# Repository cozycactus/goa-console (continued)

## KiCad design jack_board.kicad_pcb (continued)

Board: 2 copper layers, 8 parts (3 on the bottom side), 8 nets, no tracks yet.

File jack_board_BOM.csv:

"Qty","Value","Footprint","MPN","DNP","References"
"2","100p C0G","Capacitor_SMD:C_0805_2012Metric","","","C8 C9"
"1","Main board link 2x5","Connector_IDC:IDC-Header_2x05_P2.54mm_Vertical","Wurth 61201021621 (2x5 box header)","","CN5"
"1","Line in TRS","Connector_Audio:Jack_6.35mm_Neutrik_NJ6FD-V_Vertical","Neutrik NJ6FD-V","","J1"
"1","Insert TRS switched","Connector_Audio:Jack_6.35mm_Neutrik_NJ6FD-V_Vertical","Neutrik NJ6FD-V","","J2"
"1","Direct out TRS","Connector_Audio:Jack_6.35mm_Neutrik_NJ6FD-V_Vertical","Neutrik NJ6FD-V","","J5"

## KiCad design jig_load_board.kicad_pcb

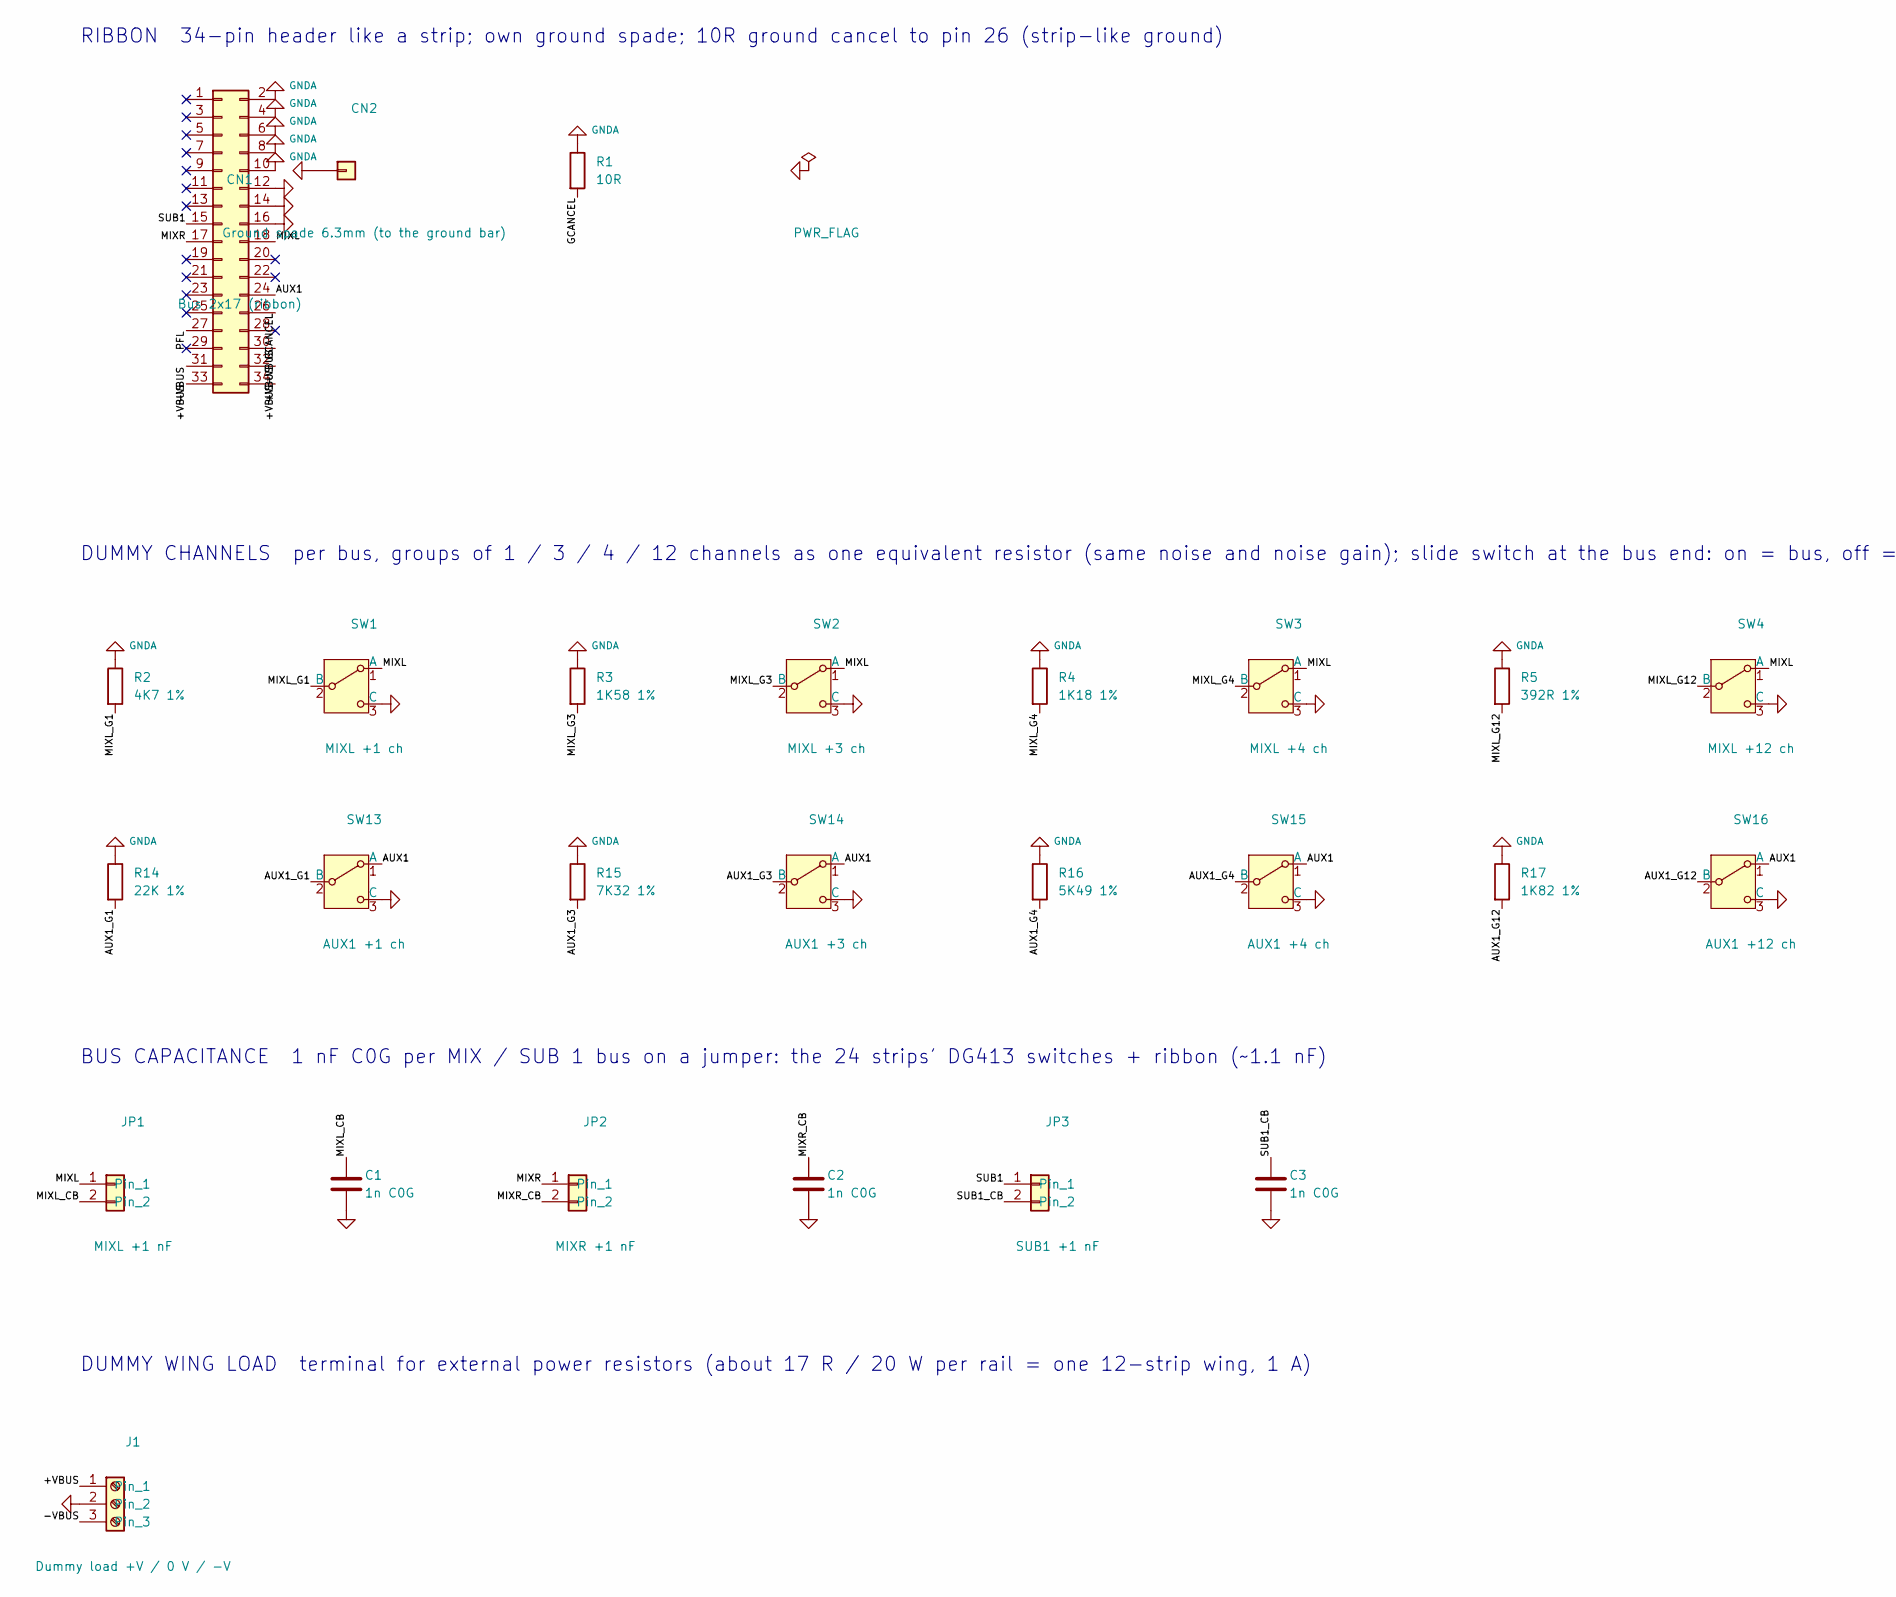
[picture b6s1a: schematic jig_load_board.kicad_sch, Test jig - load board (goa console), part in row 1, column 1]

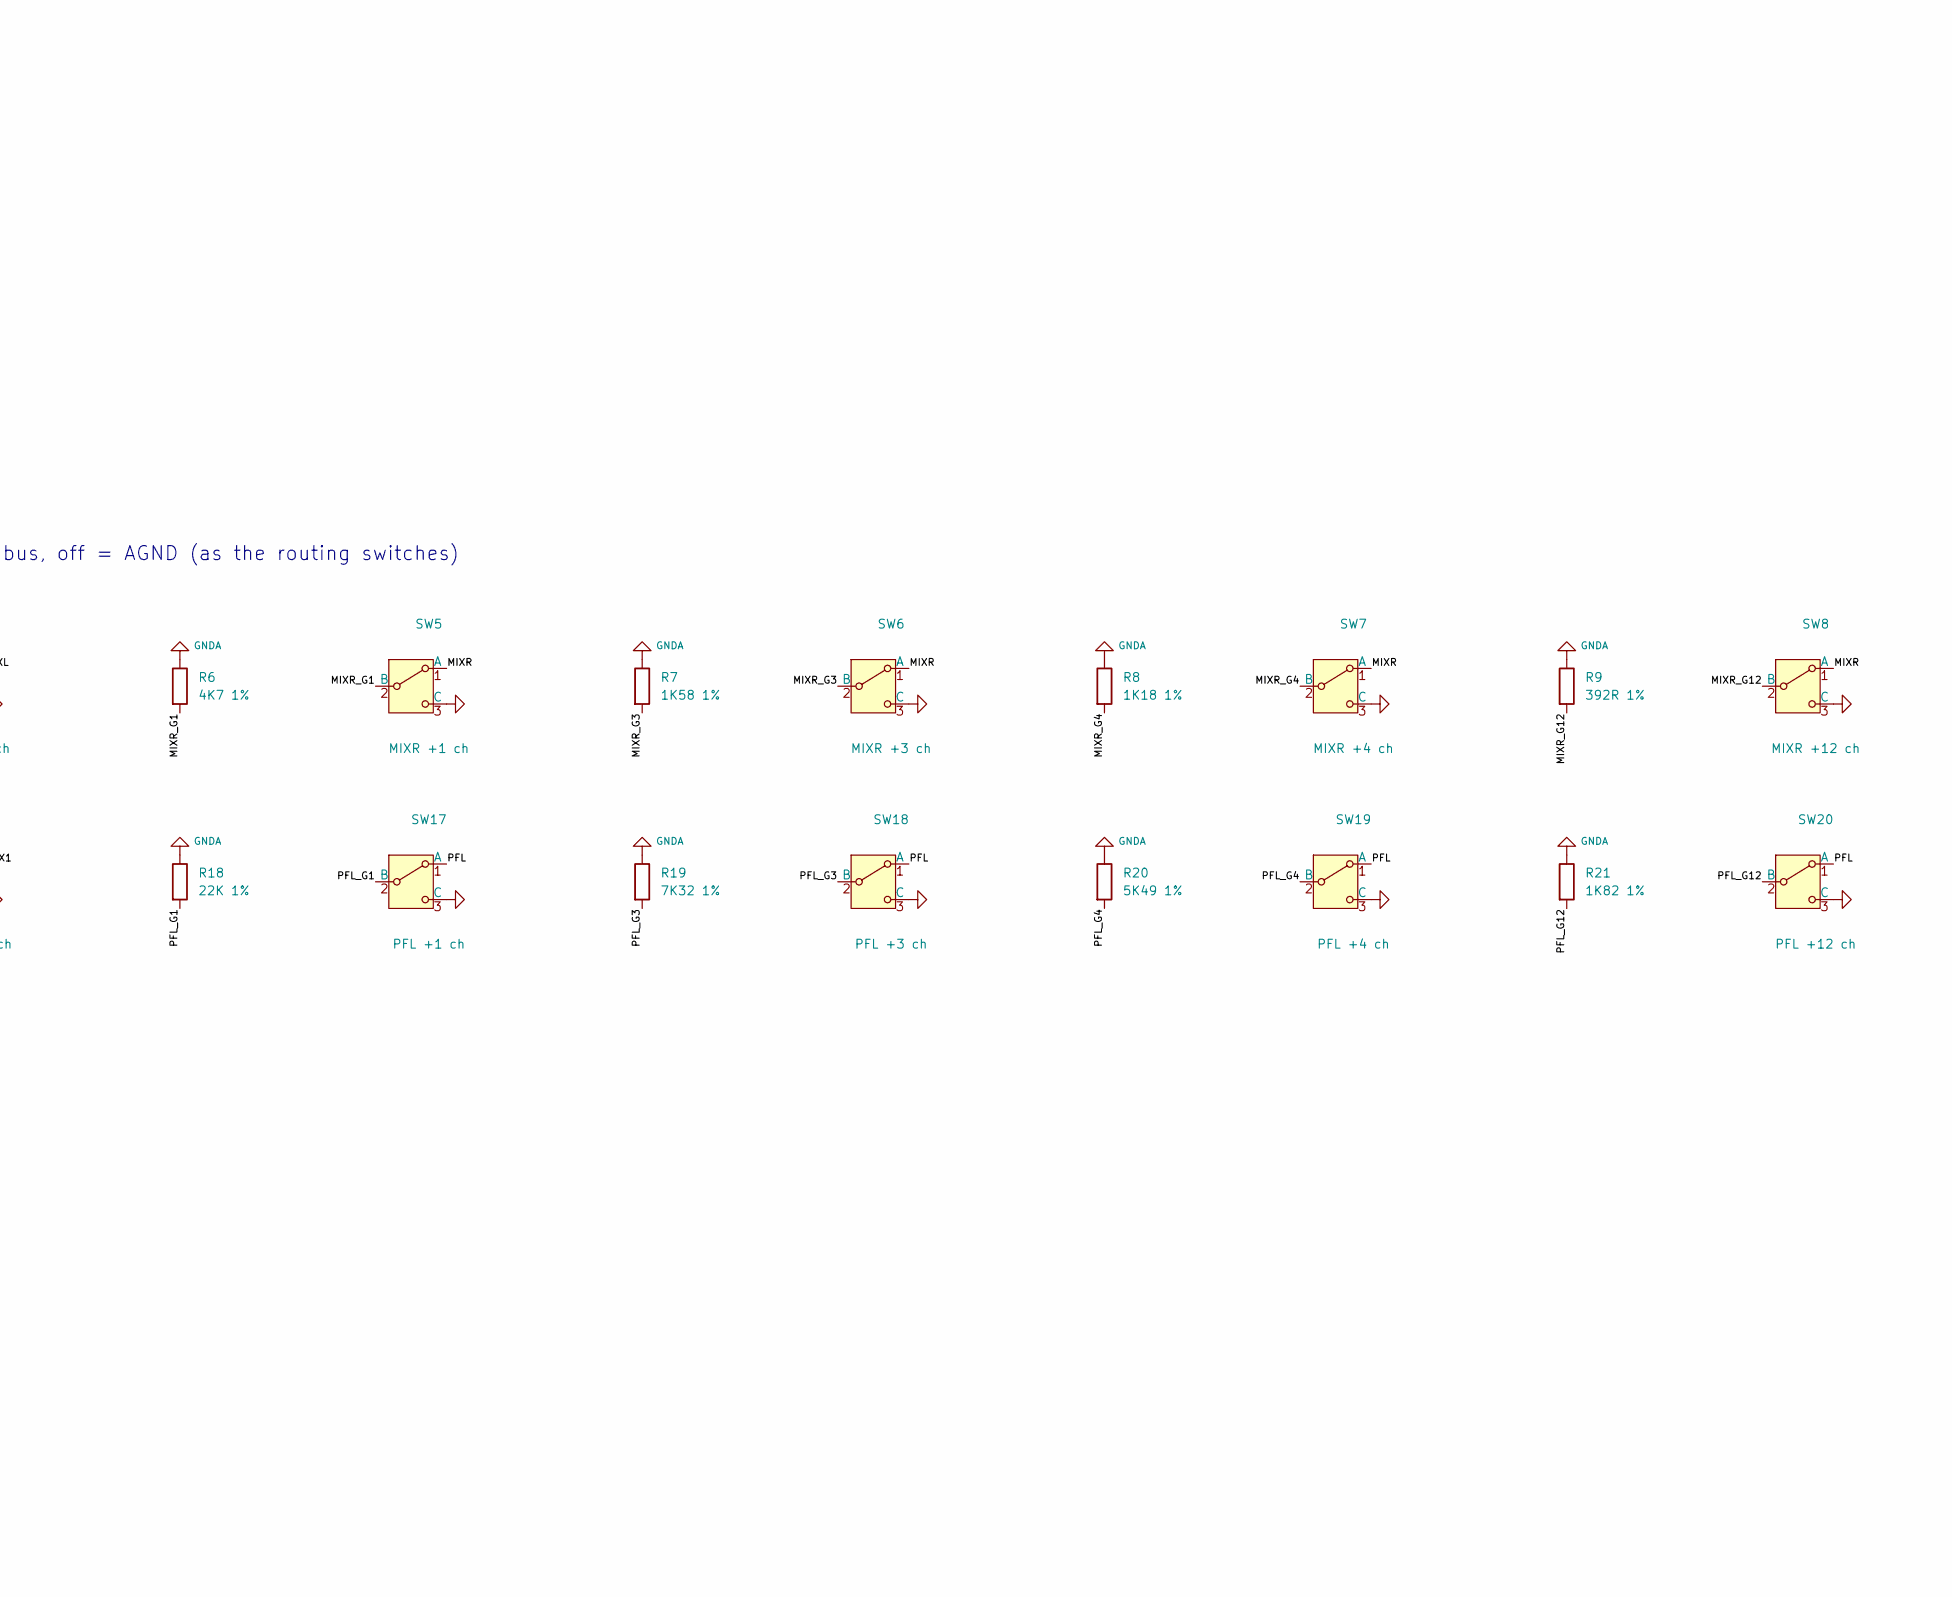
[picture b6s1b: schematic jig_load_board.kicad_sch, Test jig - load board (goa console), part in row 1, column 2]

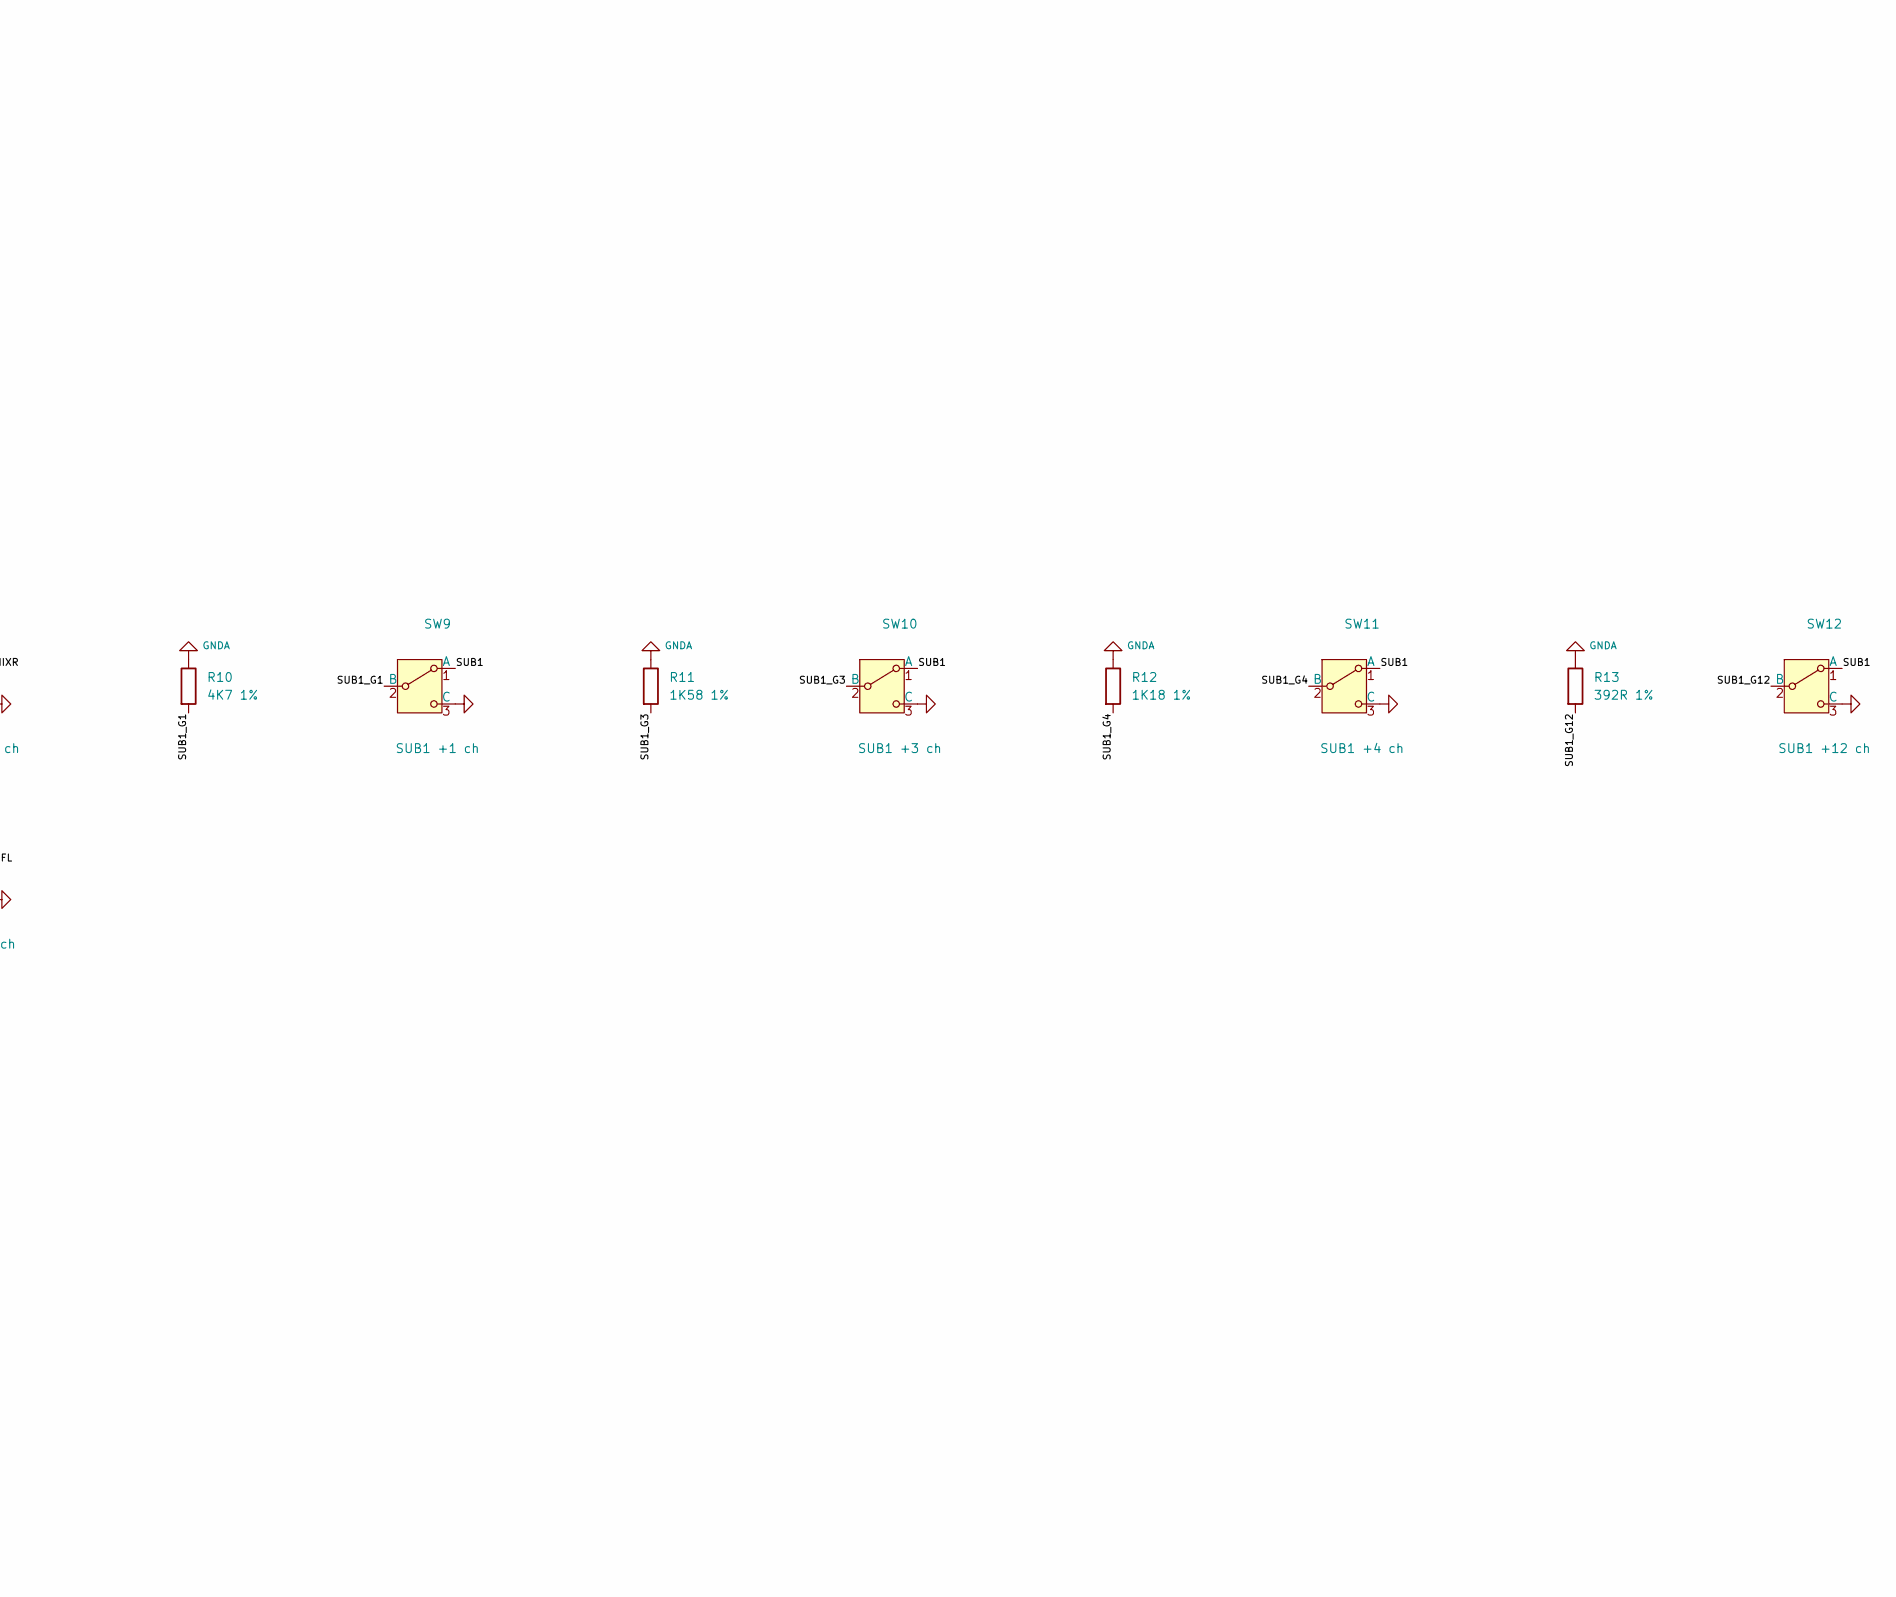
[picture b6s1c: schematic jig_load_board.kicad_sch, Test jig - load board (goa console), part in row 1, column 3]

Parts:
C1, C2, C3: 1n C0G; C_0805_2012Metric; MPN KEMET C0805C102J5GACTU
CN1: Bus 2x17 (ribbon); IDC-Header_2x17_P2.54mm_Vertical; MPN Wurth 61203421621 (2x17 box header)
CN2: Ground spade 6.3mm (to the ground bar); Keystone_1287-ST_FastOn_Tab_6.35mm; MPN Keystone 1287-ST
J1: Dummy load +V / 0 V / -V; TerminalBlock_Phoenix_MKDS-1,5-3-5.08_1x03_P5.08mm_Horizont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; MPN Phoenix MKDS 1,5/3-5,08
JP1: MIXL +1 nF; PinHeader_1x02_P2.54mm_Vertical; MPN 2.54 mm header + shunt
JP2: MIXR +1 nF; PinHeader_1x02_P2.54mm_Vertical; MPN 2.54 mm header + shunt
JP3: SUB1 +1 nF; PinHeader_1x02_P2.54mm_Vertical; MPN 2.54 mm header + shunt
R1: 10R; R_0805_2012Metric
R2, R6, R10: 4K7 1%; R_0805_2012Metric
R3, R7, R11: 1K58 1%; R_0805_2012Metric
R4, R8, R12: 1K18 1%; R_0805_2012Metric
R5, R9, R13: 392R 1%; R_0805_2012Metric
R14, R18: 22K 1%; R_0805_2012Metric
R15, R19: 7K32 1%; R_0805_2012Metric
R16, R20: 5K49 1%; R_0805_2012Metric
R17, R21: 1K82 1%; R_0805_2012Metric
SW1: MIXL +1 ch; SW_Slide_SPDT_Straight_CK_OS102011MS2Q; MPN C&K OS102011MS2QN1
SW2: MIXL +3 ch; SW_Slide_SPDT_Straight_CK_OS102011MS2Q; MPN C&K OS102011MS2QN1
SW3: MIXL +4 ch; SW_Slide_SPDT_Straight_CK_OS102011MS2Q; MPN C&K OS102011MS2QN1
SW4: MIXL +12 ch; SW_Slide_SPDT_Straight_CK_OS102011MS2Q; MPN C&K OS102011MS2QN1
SW5: MIXR +1 ch; SW_Slide_SPDT_Straight_CK_OS102011MS2Q; MPN C&K OS102011MS2QN1
SW6: MIXR +3 ch; SW_Slide_SPDT_Straight_CK_OS102011MS2Q; MPN C&K OS102011MS2QN1
SW7: MIXR +4 ch; SW_Slide_SPDT_Straight_CK_OS102011MS2Q; MPN C&K OS102011MS2QN1
SW8: MIXR +12 ch; SW_Slide_SPDT_Straight_CK_OS102011MS2Q; MPN C&K OS102011MS2QN1
SW9: SUB1 +1 ch; SW_Slide_SPDT_Straight_CK_OS102011MS2Q; MPN C&K OS102011MS2QN1
SW10: SUB1 +3 ch; SW_Slide_SPDT_Straight_CK_OS102011MS2Q; MPN C&K OS102011MS2QN1
SW11: SUB1 +4 ch; SW_Slide_SPDT_Straight_CK_OS102011MS2Q; MPN C&K OS102011MS2QN1
SW12: SUB1 +12 ch; SW_Slide_SPDT_Straight_CK_OS102011MS2Q; MPN C&K OS102011MS2QN1
SW13: AUX1 +1 ch; SW_Slide_SPDT_Straight_CK_OS102011MS2Q; MPN C&K OS102011MS2QN1
SW14: AUX1 +3 ch; SW_Slide_SPDT_Straight_CK_OS102011MS2Q; MPN C&K OS102011MS2QN1
SW15: AUX1 +4 ch; SW_Slide_SPDT_Straight_CK_OS102011MS2Q; MPN C&K OS102011MS2QN1
SW16: AUX1 +12 ch; SW_Slide_SPDT_Straight_CK_OS102011MS2Q; MPN C&K OS102011MS2QN1
SW17: PFL +1 ch; SW_Slide_SPDT_Straight_CK_OS102011MS2Q; MPN C&K OS102011MS2QN1
SW18: PFL +3 ch; SW_Slide_SPDT_Straight_CK_OS102011MS2Q; MPN C&K OS102011MS2QN1
SW19: PFL +4 ch; SW_Slide_SPDT_Straight_CK_OS102011MS2Q; MPN C&K OS102011MS2QN1
SW20: PFL +12 ch; SW_Slide_SPDT_Straight_CK_OS102011MS2Q; MPN C&K OS102011MS2QN1

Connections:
/+VBUS: CN1.32, CN1.33, CN1.34, J1.1
/-VBUS: CN1.30, CN1.31, J1.3
/AUX1: CN1.24, SW13.1 (A), SW14.1 (A), SW15.1 (A), SW16.1 (A)
/AUX1_G1: R14.2, SW13.2 (B)
/AUX1_G3: R15.2, SW14.2 (B)
/AUX1_G4: R16.2, SW15.2 (B)
/AUX1_G12: R17.2, SW16.2 (B)
/GCANCEL: CN1.26, R1.2
/MIXL: CN1.18, JP1.1, SW1.1 (A), SW2.1 (A), SW3.1 (A), SW4.1 (A)
/MIXL_CB: C1.1, JP1.2
/MIXL_G1: R2.2, SW1.2 (B)
/MIXL_G3: R3.2, SW2.2 (B)
/MIXL_G4: R4.2, SW3.2 (B)
/MIXL_G12: R5.2, SW4.2 (B)
/MIXR: CN1.17, JP2.1, SW5.1 (A), SW6.1 (A), SW7.1 (A), SW8.1 (A)
/MIXR_CB: C2.1, JP2.2
/MIXR_G1: R6.2, SW5.2 (B)
/MIXR_G3: R7.2, SW6.2 (B)
/MIXR_G4: R8.2, SW7.2 (B)
/MIXR_G12: R9.2, SW8.2 (B)
/PFL: CN1.27, SW17.1 (A), SW18.1 (A), SW19.1 (A), SW20.1 (A)
/PFL_G1: R18.2, SW17.2 (B)
/PFL_G3: R19.2, SW18.2 (B)
/PFL_G4: R20.2, SW19.2 (B)
/PFL_G12: R21.2, SW20.2 (B)
/SUB1: CN1.15, JP3.1, SW9.1 (A), SW10.1 (A), SW11.1 (A), SW12.1 (A)
/SUB1_CB: C3.1, JP3.2
/SUB1_G1: R10.2, SW9.2 (B)
/SUB1_G3: R11.2, SW10.2 (B)
/SUB1_G4: R12.2, SW11.2 (B)
/SUB1_G12: R13.2, SW12.2 (B)
GNDA: C1.2, C2.2, C3.2, CN1.2, CN1.4, CN1.6, CN1.8, CN1.10, CN1.12, CN1.14, CN1.16, CN2.1, J1.2, R1.1, R2.1, R3.1, R4.1, R5.1, R6.1, R7.1, R8.1, R9.1, R10.1, R11.1, R12.1, R13.1, R14.1, R15.1, R16.1, R17.1, R18.1, R19.1, R20.1, R21.1, SW1.3 (C), SW2.3 (C), SW3.3 (C), SW4.3 (C), SW5.3 (C), SW6.3 (C), SW7.3 (C), SW8.3 (C), SW9.3 (C), SW10.3 (C), SW11.3 (C), SW12.3 (C), SW13.3 (C), SW14.3 (C), SW15.3 (C), SW16.3 (C), SW17.3 (C), SW18.3 (C), SW19.3 (C), SW20.3 (C)

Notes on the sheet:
RIBBON 34-pin header like a strip; own ground spade; 10R ground cancel to pin 26 (strip-like ground)
DUMMY CHANNELS per bus, groups of 1 / 3 / 4 / 12 channels as one equivalent resistor (same noise and noise gain); slide switch at the bus end: on = bus, off = AGND (as the routing switches)
BUS CAPACITANCE 1 nF C0G per MIX / SUB 1 bus on a jumper: the 24 strips' DG413 switches + ribbon (~1.1 nF)
DUMMY WING LOAD terminal for external power resistors (about 17 R / 20 W per rail = one 12-strip wing, 1 A)

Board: 2 copper layers, 54 parts (0 on the bottom side), 32 nets, no tracks yet.

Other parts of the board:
H1, H2, H3, H4: M3 standoff; MountingHole_3.2mm_M3

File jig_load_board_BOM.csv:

"Qty","Value","Footprint","MPN","DNP","References"
"3","1n C0G","Capacitor_SMD:C_0805_2012Metric","KEMET C0805C102J5GACTU","","C1 C2 C3"
"1","Bus 2x17 (ribbon)","Connector_IDC:IDC-Header_2x17_P2.54mm_Vertical","Wurth 61203421621 (2x17 box header)","","CN1"
"1","Ground spade 6.3mm (to the ground bar)","goa-console:Keystone_1287-ST_FastOn_Tab_6.35mm","Keystone 1287-ST","","CN2"
"1","Dummy load +V / 0 V / -V","TerminalBlock_Phoenix:TerminalBlock_Phoenix_MKDS-1,5-3-5.08_1x03_P5.08mm_Horizontal","Phoenix MKDS 1,5/3-5,08","","J1"
"1","MIXL +1 nF","Connector_PinHeader_2.54mm:PinHeader_1x02_P2.54mm_Vertical","2.54 mm header + shunt","","JP1"
"1","MIXR +1 nF","Connector_PinHeader_2.54mm:PinHeader_1x02_P2.54mm_Vertical","2.54 mm header + shunt","","JP2"
"1","SUB1 +1 nF","Connector_PinHeader_2.54mm:PinHeader_1x02_P2.54mm_Vertical","2.54 mm header + shunt","","JP3"
"1","10R","Resistor_SMD:R_0805_2012Metric","","","R1"
"3","4K7 1%","Resistor_SMD:R_0805_2012Metric","","","R2 R6 R10"
"3","1K58 1%","Resistor_SMD:R_0805_2012Metric","","","R3 R7 R11"
"3","1K18 1%","Resistor_SMD:R_0805_2012Metric","","","R4 R8 R12"
"3","392R 1%","Resistor_SMD:R_0805_2012Metric","","","R5 R9 R13"
"2","22K 1%","Resistor_SMD:R_0805_2012Metric","","","R14 R18"
"2","7K32 1%","Resistor_SMD:R_0805_2012Metric","","","R15 R19"
"2","5K49 1%","Resistor_SMD:R_0805_2012Metric","","","R16 R20"
"2","1K82 1%","Resistor_SMD:R_0805_2012Metric","","","R17 R21"
"1","MIXL +1 ch","Button_Switch_THT:SW_Slide_SPDT_Straight_CK_OS102011MS2Q","C&K OS102011MS2QN1","","SW1"
"1","MIXL +3 ch","Button_Switch_THT:SW_Slide_SPDT_Straight_CK_OS102011MS2Q","C&K OS102011MS2QN1","","SW2"
"1","MIXL +4 ch","Button_Switch_THT:SW_Slide_SPDT_Straight_CK_OS102011MS2Q","C&K OS102011MS2QN1","","SW3"
"1","MIXL +12 ch","Button_Switch_THT:SW_Slide_SPDT_Straight_CK_OS102011MS2Q","C&K OS102011MS2QN1","","SW4"
"1","MIXR +1 ch","Button_Switch_THT:SW_Slide_SPDT_Straight_CK_OS102011MS2Q","C&K OS102011MS2QN1","","SW5"
"1","MIXR +3 ch","Button_Switch_THT:SW_Slide_SPDT_Straight_CK_OS102011MS2Q","C&K OS102011MS2QN1","","SW6"
"1","MIXR +4 ch","Button_Switch_THT:SW_Slide_SPDT_Straight_CK_OS102011MS2Q","C&K OS102011MS2QN1","","SW7"
"1","MIXR +12 ch","Button_Switch_THT:SW_Slide_SPDT_Straight_CK_OS102011MS2Q","C&K OS102011MS2QN1","","SW8"
"1","SUB1 +1 ch","Button_Switch_THT:SW_Slide_SPDT_Straight_CK_OS102011MS2Q","C&K OS102011MS2QN1","","SW9"
"1","SUB1 +3 ch","Button_Switch_THT:SW_Slide_SPDT_Straight_CK_OS102011MS2Q","C&K OS102011MS2QN1","","SW10"
"1","SUB1 +4 ch","Button_Switch_THT:SW_Slide_SPDT_Straight_CK_OS102011MS2Q","C&K OS102011MS2QN1","","SW11"
"1","SUB1 +12 ch","Button_Switch_THT:SW_Slide_SPDT_Straight_CK_OS102011MS2Q","C&K OS102011MS2QN1","","SW12"
"1","AUX1 +1 ch","Button_Switch_THT:SW_Slide_SPDT_Straight_CK_OS102011MS2Q","C&K OS102011MS2QN1","","SW13"
"1","AUX1 +3 ch","Button_Switch_THT:SW_Slide_SPDT_Straight_CK_OS102011MS2Q","C&K OS102011MS2QN1","","SW14"
"1","AUX1 +4 ch","Button_Switch_THT:SW_Slide_SPDT_Straight_CK_OS102011MS2Q","C&K OS102011MS2QN1","","SW15"
"1","AUX1 +12 ch","Button_Switch_THT:SW_Slide_SPDT_Straight_CK_OS102011MS2Q","C&K OS102011MS2QN1","","SW16"
"1","PFL +1 ch","Button_Switch_THT:SW_Slide_SPDT_Straight_CK_OS102011MS2Q","C&K OS102011MS2QN1","","SW17"
"1","PFL +3 ch","Button_Switch_THT:SW_Slide_SPDT_Straight_CK_OS102011MS2Q","C&K OS102011MS2QN1","","SW18"
"1","PFL +4 ch","Button_Switch_THT:SW_Slide_SPDT_Straight_CK_OS102011MS2Q","C&K OS102011MS2QN1","","SW19"
"1","PFL +12 ch","Button_Switch_THT:SW_Slide_SPDT_Straight_CK_OS102011MS2Q","C&K OS102011MS2QN1","","SW20"
